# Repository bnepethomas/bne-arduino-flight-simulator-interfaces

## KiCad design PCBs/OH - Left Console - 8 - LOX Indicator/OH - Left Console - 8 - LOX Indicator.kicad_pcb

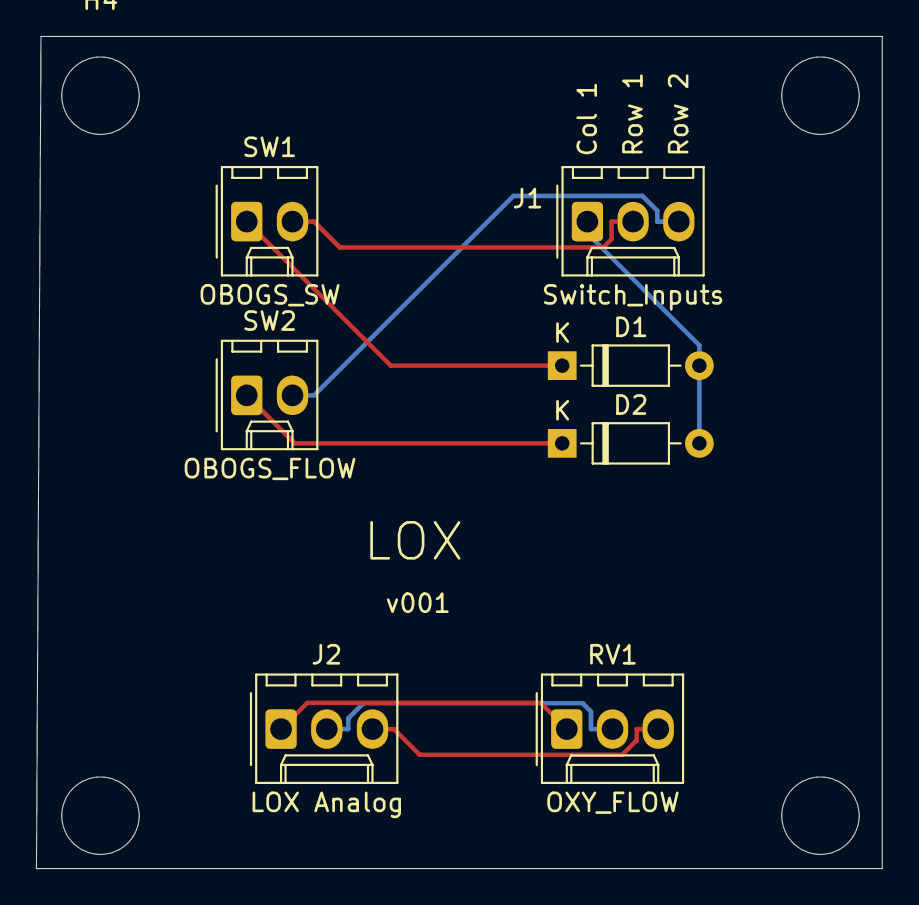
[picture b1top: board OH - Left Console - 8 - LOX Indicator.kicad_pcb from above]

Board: 2 copper layers, 47.0 x 46.2 mm, 11 parts (0 on the bottom side), 8 nets.

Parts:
D1, D2: D; D_Signal_P7.62mm_Horizontal
H1, H2, H3, H4: MountingHole; MountingHole_4.3mm_M4
J1: Switch_Inputs; Molex_1x03_P2.54mm_Vertical
J2: LOX Analog; Molex_1x03_P2.54mm_Vertical
RV1: OXY_FLOW; Molex_1x03_P2.54mm_Vertical
SW1: OBOGS_SW; Molex_1x02_P2.54mm_Vertical
SW2: OBOGS_FLOW; Molex_1x02_P2.54mm_Vertical

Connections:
/+5V: J2.1, RV1.1
/Col1: D1.2, D2.2, J1.1
/GND: J2.3, RV1.3
/Row1: J1.2, SW1.2
/Row2: J1.3, SW2.2
unnamed: D1.1, SW1.1
unnamed: D2.1, SW2.1
unnamed: J2.2, RV1.2

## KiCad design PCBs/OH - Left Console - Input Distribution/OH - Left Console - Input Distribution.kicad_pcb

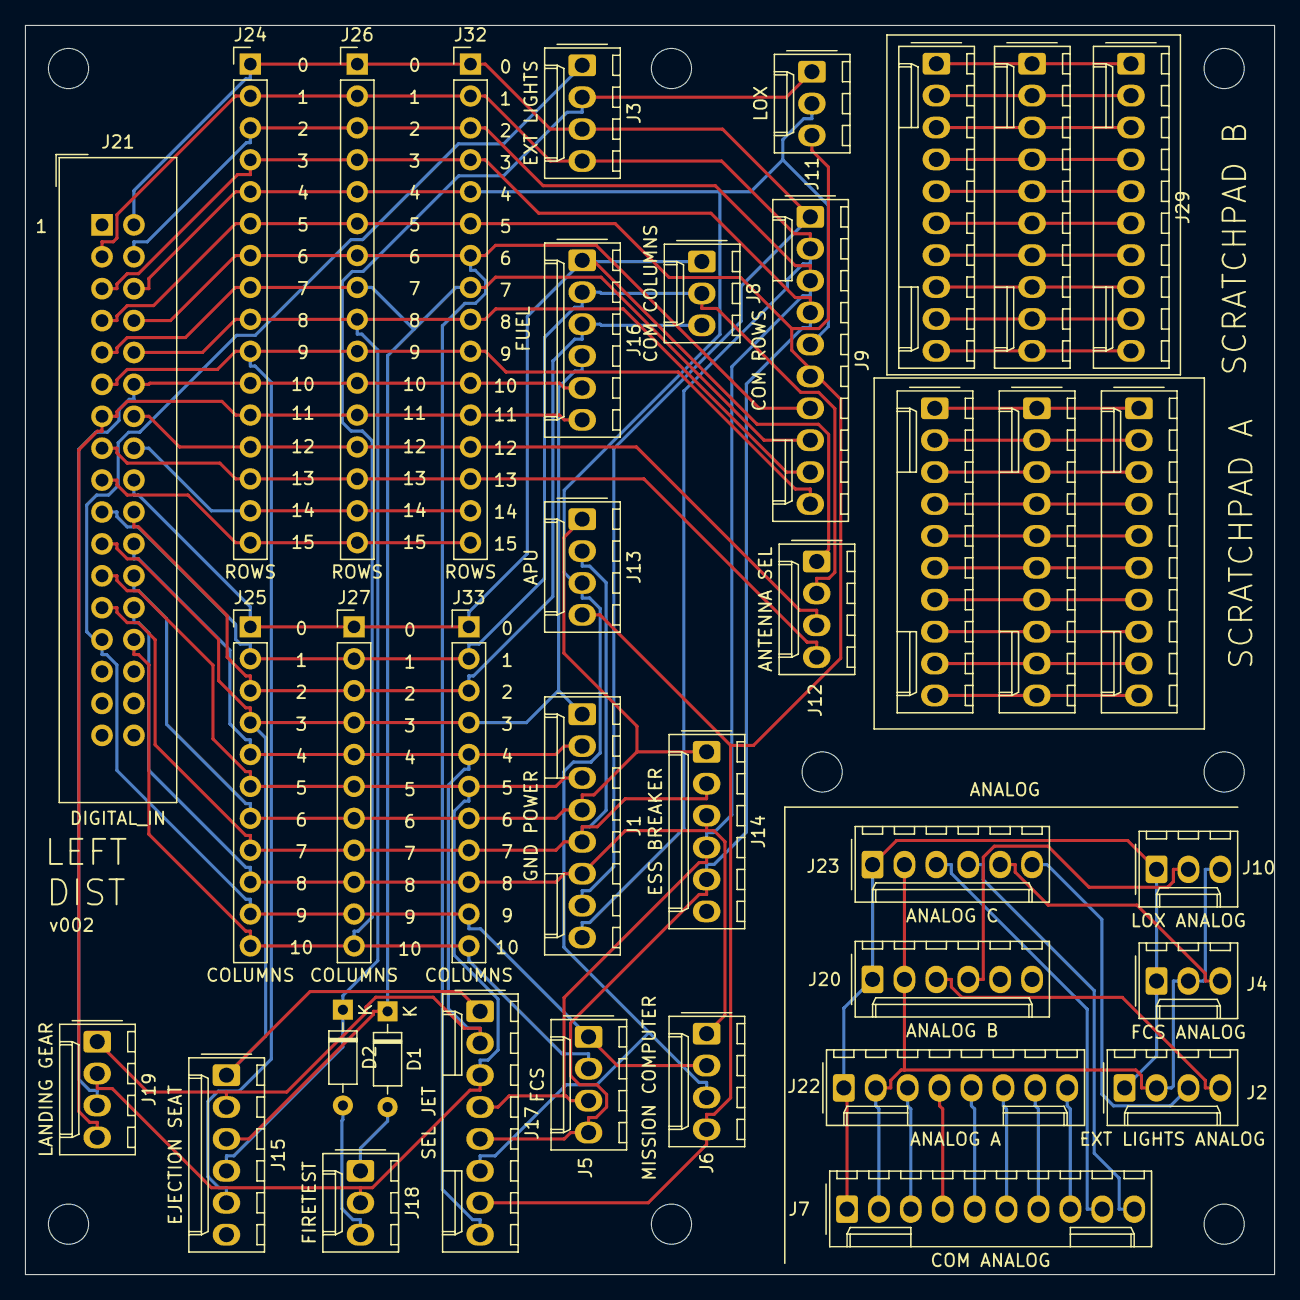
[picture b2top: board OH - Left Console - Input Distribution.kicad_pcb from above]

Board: 2 copper layers, 99.4 x 99.4 mm, 45 parts (0 on the bottom side), 63 nets.

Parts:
D1, D2: D; D_Signal_P7.62mm_Horizontal
H1, H2, H3, H4, H5, H6, H7, H8: MountingHole; MountingHole_3.2mm_M3
J1: GND POWER; Molex_1x08_P2.54mm_Vertical
J2: EXT LIGHTS ANALOG; Molex_1x04_P2.54mm_Vertical
J3: EXT LIGHTS; Molex_1x04_P2.54mm_Vertical
J4: FCS ANALOG; Molex_1x03_P2.54mm_Vertical
J5: FCS; Molex_1x04_P2.54mm_Vertical
J6: MISSION COMPUTER; Molex_1x04_P2.54mm_Vertical
J7: COM ANALOG; Molex_1x10_P2.54mm_Vertical
J8: COM COLUMNS; Molex_1x03_P2.54mm_Vertical
J9: COM ROWS; Molex_1x10_P2.54mm_Vertical
J10: LOX ANALOG; Molex_1x03_P2.54mm_Vertical
J11: LOX; Molex_1x03_P2.54mm_Vertical
J12: ANTENNA SEL; Molex_1x04_P2.54mm_Vertical
J13: APU; Molex_1x04_P2.54mm_Vertical
J14: ESS BREAKER; Molex_1x06_P2.54mm_Vertical
J15: EJECTION SEAT; Molex_1x06_P2.54mm_Vertical
J16: FUEL; Molex_1x06_P2.54mm_Vertical
J17: SEL JET; Molex_1x08_P2.54mm_Vertical
J18: FIRETEST; Molex_1x03_P2.54mm_Vertical
J19: LANDING GEAR; Molex_1x04_P2.54mm_Vertical
J20: ANALOG B; Molex_1x06_P2.54mm_Vertical
J21: DIGITAL_IN; IDC-Header_2x17_P2.54mm_Vertical
J22: ANALOG A; Molex_1x08_P2.54mm_Vertical
J23: ANALOG C; Molex_1x06_P2.54mm_Vertical
J24, J26, J32: ROWS; PinHeader_1x16_P2.54mm_Vertical
J25, J27, J33: COLUMNS; PinHeader_1x11_P2.54mm_Vertical
J28: SpareA1; Molex_1x10_P2.54mm_Vertical
J29: SpareB1; Molex_1x10_P2.54mm_Vertical
J30: SpareA2; Molex_1x10_P2.54mm_Vertical
J31: SpareB2; Molex_1x10_P2.54mm_Vertical
J34: SpareA3; Molex_1x10_P2.54mm_Vertical
J35: SpareB3; Molex_1x10_P2.54mm_Vertical

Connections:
/A1: J28.1, J30.1, J34.1
/A2: J28.2, J30.2, J34.2
/A3: J28.3, J30.3, J34.3
/A4: J28.4, J30.4, J34.4
/A5: J28.5, J30.5, J34.5
/A6: J28.6, J30.6, J34.6
/A7: J28.7, J30.7, J34.7
/A8: J28.8, J30.8, J34.8
/A9: J28.9, J30.9, J34.9
/A10: J28.10, J30.10, J34.10
/ANALOG_5V: J2.1, J4.1, J7.1, J10.1, J20.1, J22.1, J23.1
/ANALOG_GND: J2.2, J4.2, J7.2, J10.3, J20.2, J22.2, J23.2
/B1: J29.1, J31.1, J35.1
/B2: J29.2, J31.2, J35.2
/B3: J29.3, J31.3, J35.3
/B4: J29.4, J31.4, J35.4
/B5: J29.5, J31.5, J35.5
/B6: J29.6, J31.6, J35.6
/B7: J29.7, J31.7, J35.7
/B8: J29.8, J31.8, J35.8
/B9: J29.9, J31.9, J35.9
/B10: J29.10, J31.10, J35.10
/COL0: J8.1, J12.1, J16.1, J21.18, J25.1, J27.1, J33.1
/COL1: J8.2, J12.2, J16.2, J21.19, J25.2, J27.2, J33.2
/COL2: J8.3, J16.3, J21.20, J25.3, J27.3, J33.3
/COL3: J1.1, J15.1, J16.4, J17.1, J21.21, J25.4, J27.4, J33.4
/COL4: J1.2, J15.2, J17.2, J19.1, J21.22, J25.5, J27.5, J33.5
/COL5: J1.3, J17.3, J18.2, J19.2, J21.23, J25.6, J27.6, J33.6
/COL6: J1.4, J13.1, J14.1, J21.24, J25.7, J27.7, J33.7
/COL7: J1.5, J13.2, J14.2, J21.25, J25.8, J27.8, J33.8
/COL8: J1.6, J6.1, J14.3, J21.26, J25.9, J27.9, J33.9
/COL9: J3.1, J5.1, J6.2, J21.27, J25.10, J27.10, J33.10
/COL10: J3.2, J5.2, J11.1, J21.28, J25.11, J27.11, J33.11
/COM_AUX: J7.9, J23.3
/COM_ICS: J7.4, J22.4
/COM_MIDS_A: J7.6, J22.6
/COM_MIDS_B: J7.7, J22.7
/COM_RWR: J7.5, J22.5
/COM_TACAN: J7.8, J22.8
/COM_VOX: J7.3, J22.3
/COM_WPN: J7.10, J23.4
/FORMATION_DIMMER: J2.4, J20.3
/OXY_FLOW: J10.2, J20.4
/POSITION_DIMMER: J2.3, J23.6
/ROW0: J1.7, J3.3, J9.1, J21.2, J24.1, J26.1, J32.1
/ROW1: J1.8, J3.4, J9.2, J21.3, J24.2, J26.2, J32.2
/ROW2: J5.3, J9.3, J14.4, J17.4, J21.4, J24.3, J26.3, J32.3
/ROW3: J5.4, J9.4, J14.5, J17.5, J21.5, J24.4, J26.4, J32.4
/ROW4: J6.3, J9.5, J11.2, J13.3, J17.6, J21.6, J24.5, J26.5, J32.5
/ROW5: J6.4, J9.6, J11.3, J13.4, J17.7, J21.7, J24.6, J26.6, J32.6
/ROW6: J9.7, J17.8, J21.8, J24.7, J26.7, J32.7
/ROW7: D1.1, J9.8, J15.3, J21.9, J24.8, J26.8, J32.8
/ROW8: D2.1, J9.9, J15.4, J21.10, J24.9, J26.9, J32.9
/ROW9: J9.10, J15.5, J21.11, J24.10, J26.10, J32.10
/ROW10: J16.5, J19.3, J21.12, J24.11, J26.11, J32.11
/ROW11: J16.6, J19.4, J21.13, J24.12, J26.12, J32.12
/ROW12: J12.3, J21.14, J24.13, J26.13, J32.13
/ROW13: J12.4, J21.15, J24.14, J26.14, J32.14
/ROW14: J21.16, J24.15, J26.15, J32.15
/ROW15: J21.17, J24.16, J26.16, J32.16
/RUD_TRIM: J4.3, J23.5
unnamed: D1.2, J18.1
unnamed: D2.2, J18.3

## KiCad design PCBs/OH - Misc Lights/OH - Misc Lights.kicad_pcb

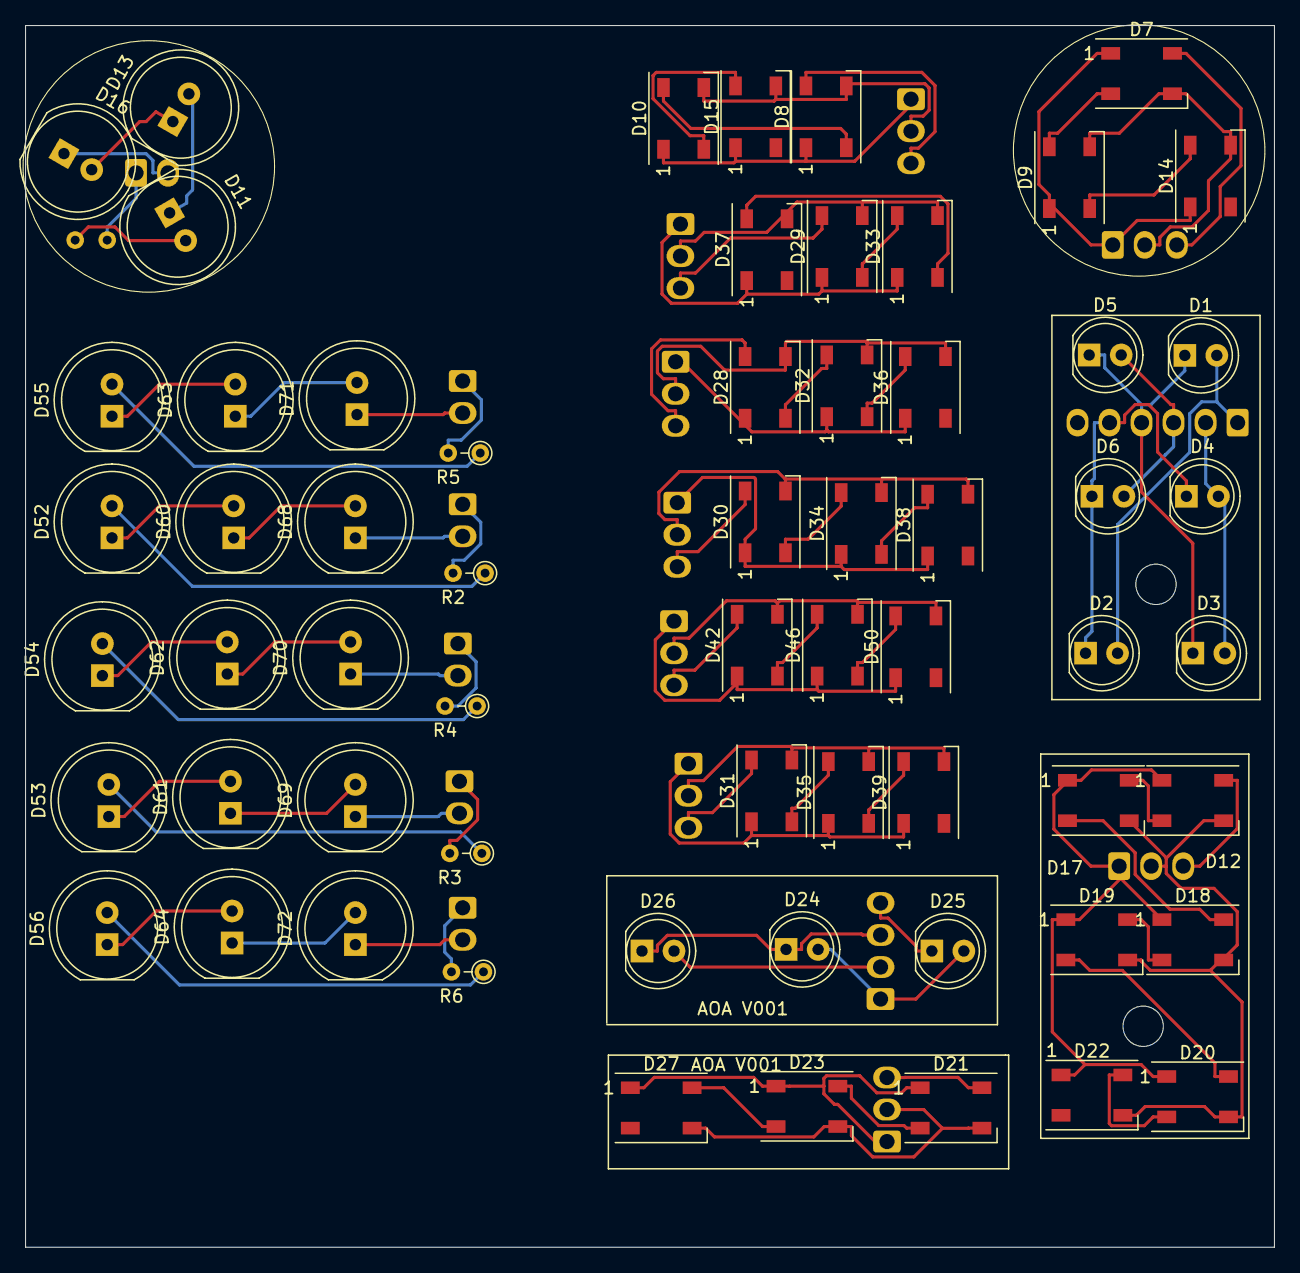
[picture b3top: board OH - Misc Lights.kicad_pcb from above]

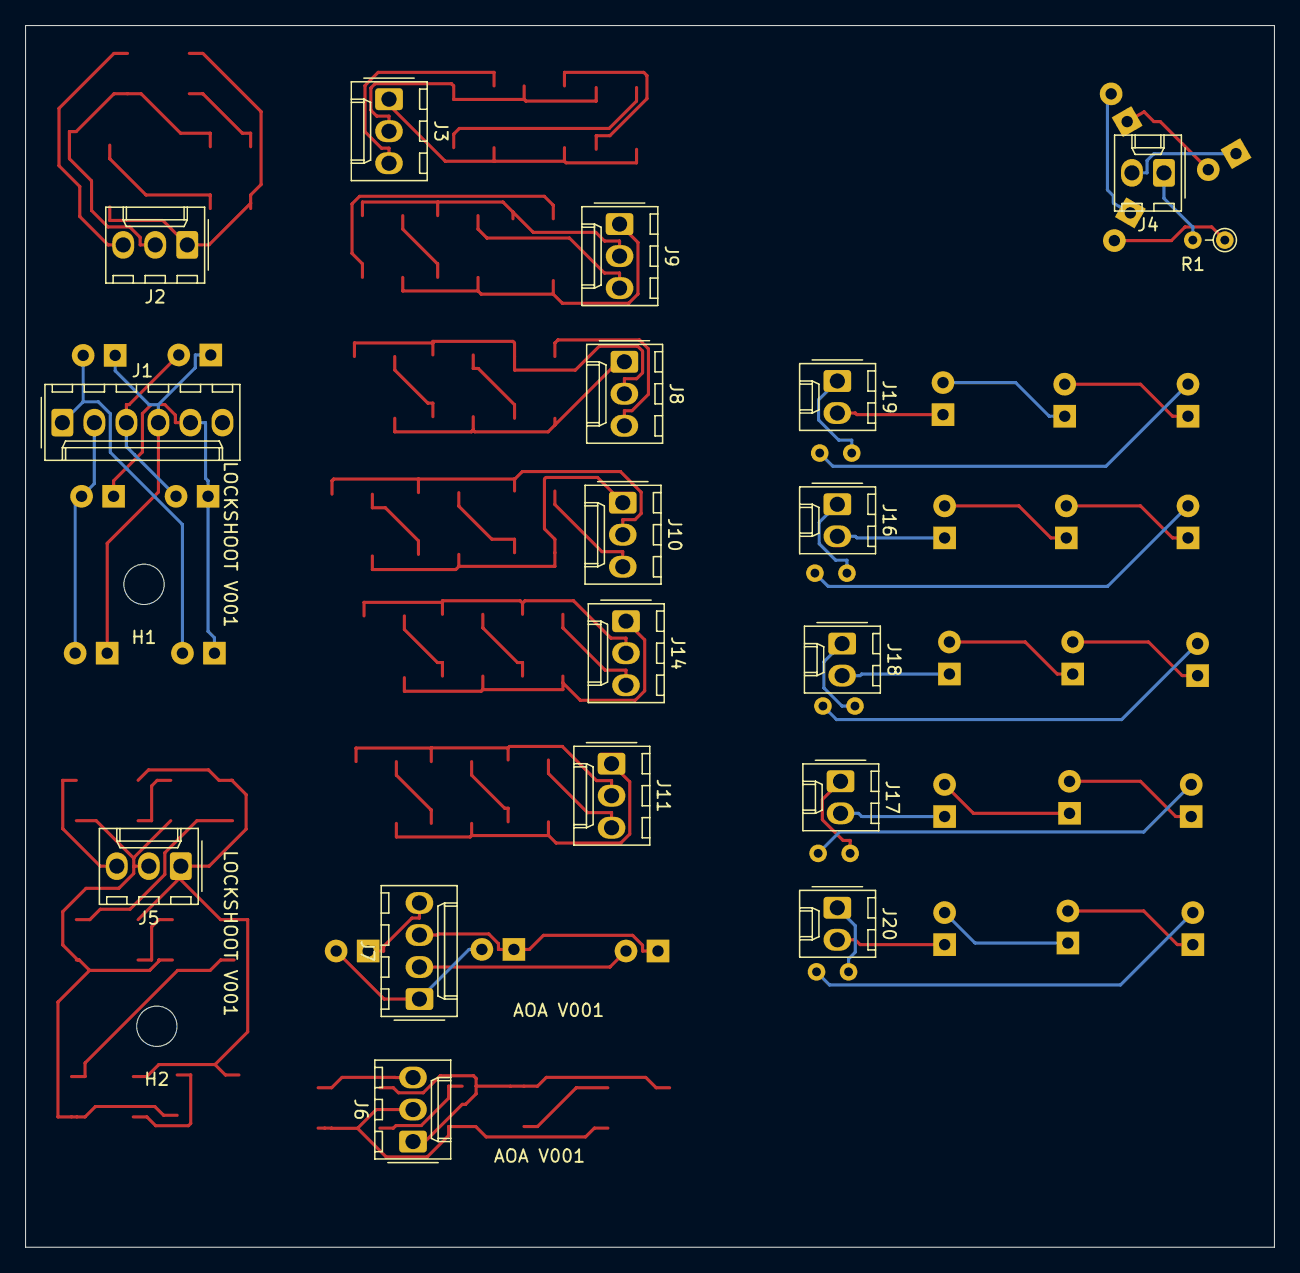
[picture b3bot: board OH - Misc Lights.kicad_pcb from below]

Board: 2 copper layers, 99.1 x 96.9 mm, 82 parts (20 on the bottom side), 87 nets.

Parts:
D1, D2, D3, D4, D5, D6, D24, D25, D26: LED; LED_D5.0mm
D7, D8, D9, D10, D12, D14, D15, D17, D18, D19, D20, D21, D22, D23, D27, D28, D29, D30, D31, D32, D33, D34, D35, D36, D37, D38, D39, D42, D46, D50: WS2812B; LED_WS2812B_PLCC4_5.0x5.0mm_P3.2mm
D11, D13, D16, D52, D53, D54, D55, D56, D60, D61, D62, D63, D64, D68, D69, D70, D71, D72: LED; LED_D8.0mm
H1, H2: MountingHole; MountingHole_3.2mm_M3
J1: Conn_01x06_Female; Molex_1x06_P2.54mm_Vertical
J2, J3, J5, J6, J8, J9, J10, J11, J14: Conn_01x03_Female; Molex_1x03_P2.54mm_Vertical
J4, J16, J17, J18, J19, J20: Conn_01x02_Female; Molex_1x02_P2.54mm_Vertical
J7: Conn_01x04_Female; Molex_1x04_P2.54mm_Vertical
R1, R2, R3, R4, R5, R6: R_US; PT_R_Axial_DIN0204_L3.6mm_D1.6mm_P2.54mm_Vertical

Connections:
/AOA_2812_+5V: D21.1, D23.1, D27.1, J6.1
/AOA_2812_GND: D21.3, D23.3, D27.3, J6.2
/AOA_2812_IN: D21.4, J6.3
/AOA_COL1: D24.2, D25.2, J7.1
/AOA_COL2: D26.2, J7.2
/AOA_ROW1: D24.1, D26.1, J7.3
/AOA_ROW2: D25.1, J7.4
/CHART_5V: J4.1, R1.2
/CHART_GND: D16.1, J4.2
/Col1: D1.2, D2.2, J1.1
/Col2: D3.2, D4.2, J1.2
/Col3: D5.2, D6.2, J1.3
/FLOOD_2812_+5V: D7.1, D9.1, D14.1, J2.1
/FLOOD_2812_GND: D7.3, D9.3, D14.3, J2.2
/FLOOD_2812_IN: D7.4, J2.3
/LOCKSHOOT_2812_+5V: D12.1, D17.1, D18.1, D19.1, D20.1, D22.1, J5.1
/LOCKSHOOT_2812_GND: D12.3, D17.3, D18.3, D19.3, D20.3, D22.3, J5.2
/LOCKSHOOT_IN: D12.4, J5.3
/Row1: D1.1, D3.1, D5.1, J1.4
/Row2: D2.1, D4.1, D6.1, J1.5
unnamed: D7.2, D9.4
unnamed: D8.4, J3.3
unnamed: D8.1, D10.1, D15.1, J3.1
unnamed: D10.2, D15.4
unnamed: D8.3, D10.3, D15.3, J3.2
unnamed: D8.2, D10.4
unnamed: D11.1, D13.2
unnamed: D11.2, R1.1
unnamed: D12.2, D17.4
unnamed: D13.1, D16.2
unnamed: D9.2, D14.4
unnamed: D17.2, D18.4
unnamed: D18.2, D19.4
unnamed: D19.2, D20.4
unnamed: D20.2, D22.4
unnamed: D21.2, D23.4
unnamed: D23.2, D27.4
unnamed: D28.1, D32.1, D36.1, J8.1
unnamed: D28.2, D32.4
unnamed: D28.3, D32.3, D36.3, J8.2
unnamed: D28.4, J8.3
unnamed: D29.1, D33.1, D37.1, J9.1
unnamed: D29.2, D33.4
unnamed: D29.3, D33.3, D37.3, J9.2
unnamed: D29.4, J9.3
unnamed: D30.1, D34.1, D38.1, J10.1
unnamed: D30.2, D34.4
unnamed: D30.3, D34.3, D38.3, J10.2
unnamed: D30.4, J10.3
unnamed: D31.1, D35.1, D39.1, J11.1
unnamed: D31.2, D35.4
unnamed: D31.3, D35.3, D39.3, J11.2
unnamed: D31.4, J11.3
unnamed: D32.2, D36.4
unnamed: D33.2, D37.4
unnamed: D34.2, D38.4
unnamed: D35.2, D39.4
unnamed: D42.1, D46.1, D50.1, J14.1
unnamed: D42.2, D46.4
unnamed: D42.3, D46.3, D50.3, J14.2
unnamed: D42.4, J14.3
unnamed: D46.2, D50.4
unnamed: D52.1, D60.2
unnamed: D52.2, R2.1
unnamed: D53.1, D61.2
unnamed: D53.2, R3.1
unnamed: D54.1, D62.2
unnamed: D54.2, R4.1
unnamed: D55.1, D63.2
unnamed: D55.2, R5.1
unnamed: D56.1, D64.2
unnamed: D56.2, R6.1
unnamed: D60.1, D68.2
unnamed: D61.1, D69.2
unnamed: D62.1, D70.2
unnamed: D63.1, D71.2
unnamed: D64.1, D72.2
unnamed: D68.1, J16.2
unnamed: D69.1, J17.2
unnamed: D70.1, J18.2
unnamed: D71.1, J19.2
unnamed: D72.1, J20.2
unnamed: J16.1, R2.2
unnamed: J17.1, R3.2
unnamed: J18.1, R4.2
unnamed: J19.1, R5.2
unnamed: J20.1, R6.2

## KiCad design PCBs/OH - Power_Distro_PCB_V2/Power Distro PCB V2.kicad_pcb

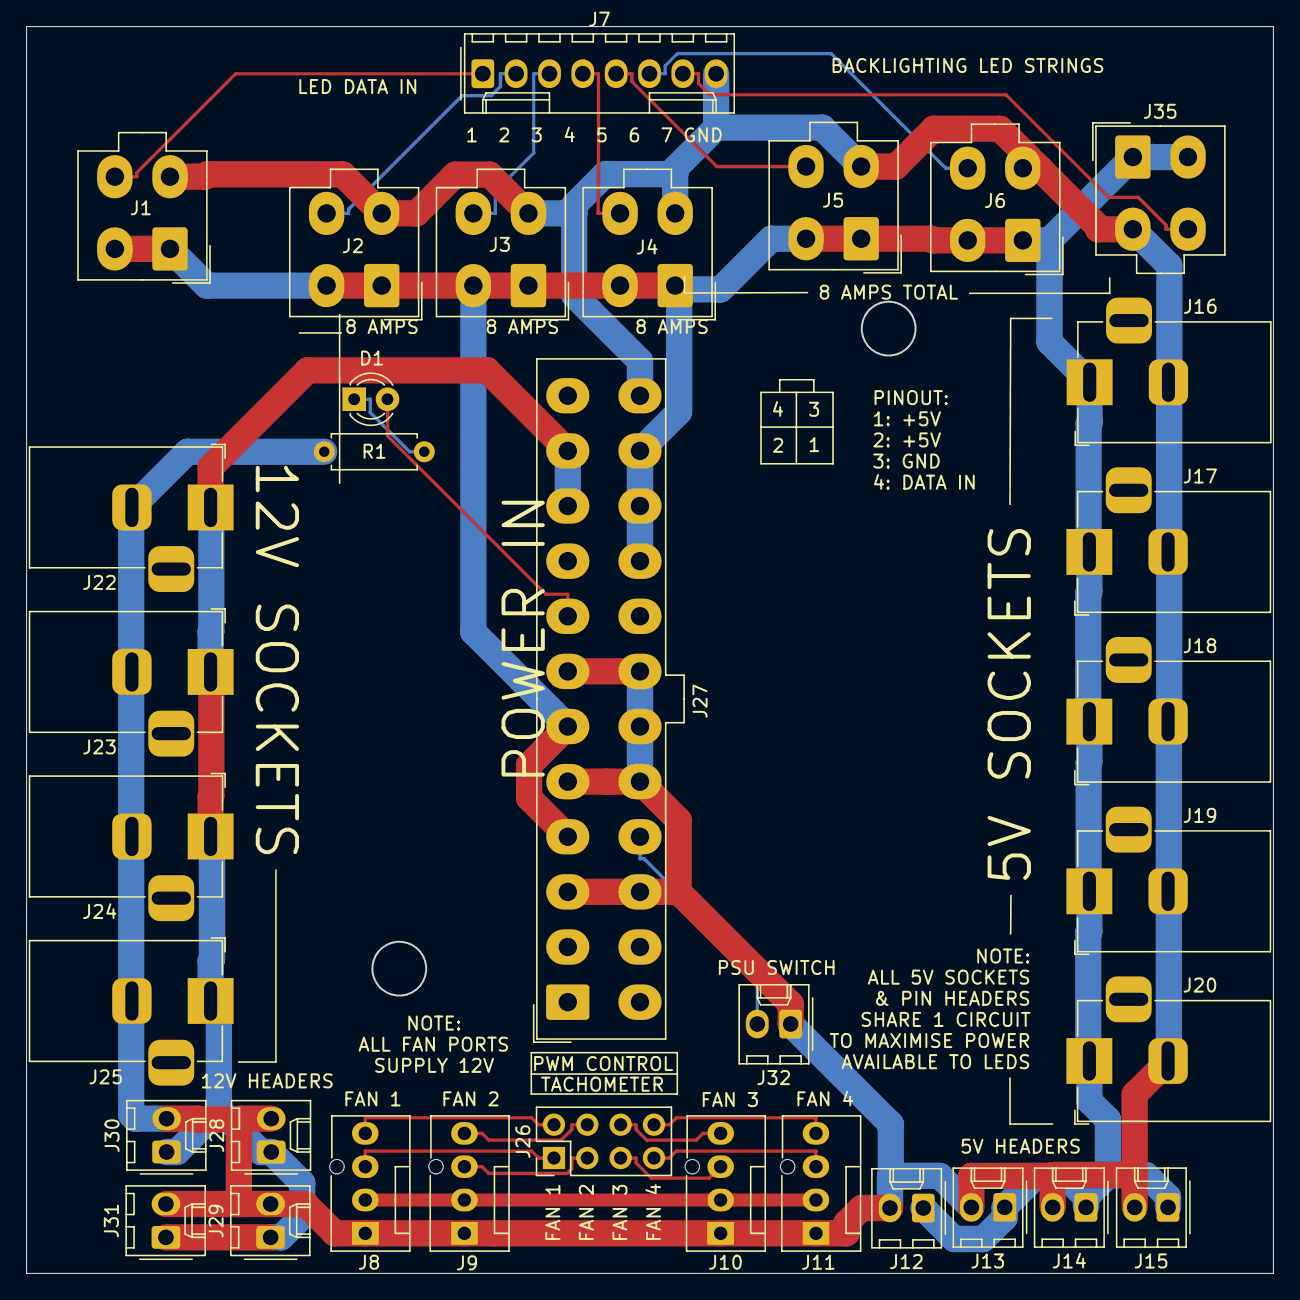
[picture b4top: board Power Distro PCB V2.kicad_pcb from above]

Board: 2 copper layers, 95.0 x 95.0 mm, 34 parts (0 on the bottom side), 22 nets.

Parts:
D1: LED; LED_D3.0mm
J1, J2, J3, J4, J5, J6, J35: Conn_01x04_Female; Molex_Mini-Fit_Jr_5566-04A_2x02_P4.20mm_Vertical
J7: Conn_01x08_Female; Molex_1x08_P2.54mm_Vertical
J8, J9, J10, J11: Conn_01x04_Female; FanPinHeader_1x04_P2.54mm_Vertical
J12, J13, J14, J15, J28, J29, J30, J31, J32: Conn_01x02_Female; Molex_KK-254_AE-6410-02A_1x02_P2.54mm_Vertical
J16, J17, J18, J19, J20, J22, J23, J24, J25: Conn_01x02_Female; BarrelJack_Horizontal
J26: Conn_01x08_Female; PinHeader_2x04_P2.54mm_Vertical
J27: Conn_01x24_Female; Molex_Mini-Fit_Jr_5566-24A_2x12_P4.20mm_Vertical
R1: R; R_Axial_DIN0207_L6.3mm_D2.5mm_P7.62mm_Horizontal

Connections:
/12VSOCKETS+: J22.1, J23.1, J24.1, J25.1, J27.10, J27.11, J28.1, J29.1, J30.1, J31.1
/FAN1Control: J8.4, J26.2
/FAN1Tach: J8.3, J26.1
/FAN2Control: J9.4, J26.4
/FAN2Tach: J9.3, J26.3
/FAN3Control: J10.4, J26.6
/FAN3Tach: J10.3, J26.5
/FAN4Control: J11.4, J26.8
/FAN4Tach: J11.3, J26.7
/FAN+: J8.2, J9.2, J10.2, J11.2
/LED5V1: J1.1, J1.2, J2.1, J2.2, J3.1, J3.2, J4.1, J4.2, J5.1, J5.2, J6.1, J6.2, J12.1, J13.1, J14.1, J15.1, J16.1, J17.1, J18.1, J19.1, J20.1, J27.4, J27.6, J27.21, J27.22, J27.23, J35.1, J35.2
/LEDDATA1: J1.4, J7.1
/LEDDATA2: J2.4, J7.2
/LEDDATA3: J3.4, J7.3
/LEDDATA4: J4.4, J7.4
/LEDDATA5: J5.4, J7.5
/LEDDATA6: J6.4, J7.6
/LEDDATA7: J7.7, J35.4
/LEDGND: J1.3, J2.3, J3.3, J4.3, J5.3, J6.3, J7.8, J8.1, J9.1, J10.1, J11.1, J12.2, J13.2, J14.2, J15.2, J16.2, J17.2, J18.2, J19.2, J20.2, J22.2, J23.2, J24.2, J25.2, J27.3, J27.5, J27.7, J27.15, J27.17, J27.18, J27.19, J27.24, J28.2, J29.2, J30.2, J31.2, J32.1, J35.3, R1.1
/PSUSW: J27.16, J32.2
/PWRGOOD: D1.2, J27.8
unnamed: D1.1, R1.2

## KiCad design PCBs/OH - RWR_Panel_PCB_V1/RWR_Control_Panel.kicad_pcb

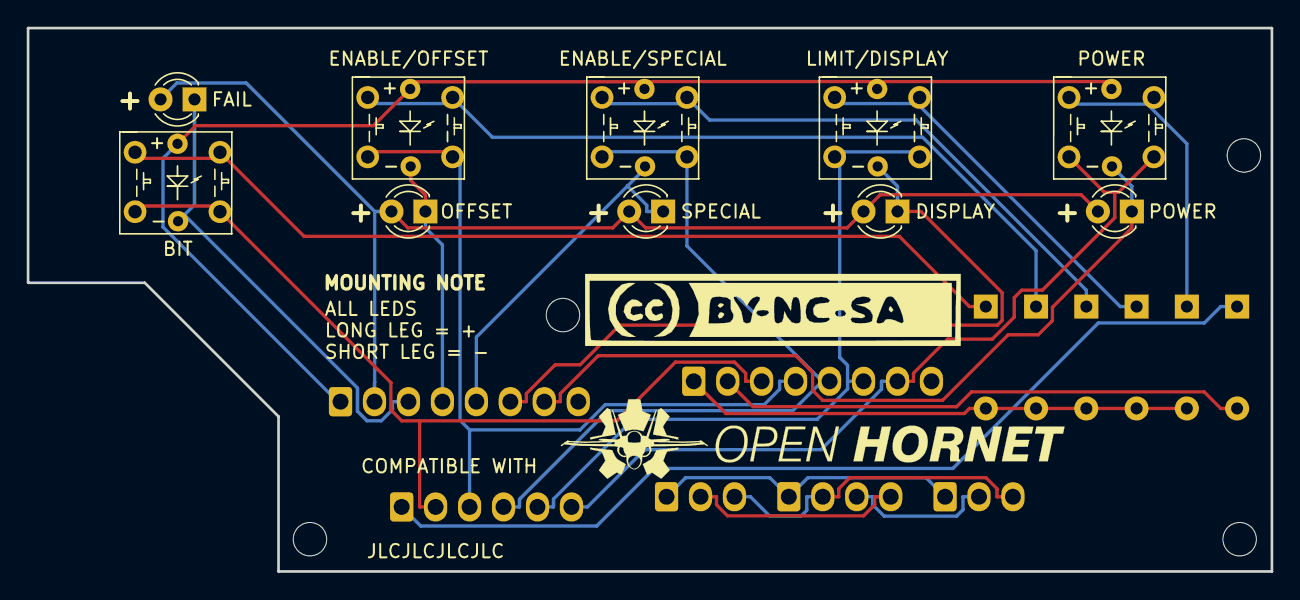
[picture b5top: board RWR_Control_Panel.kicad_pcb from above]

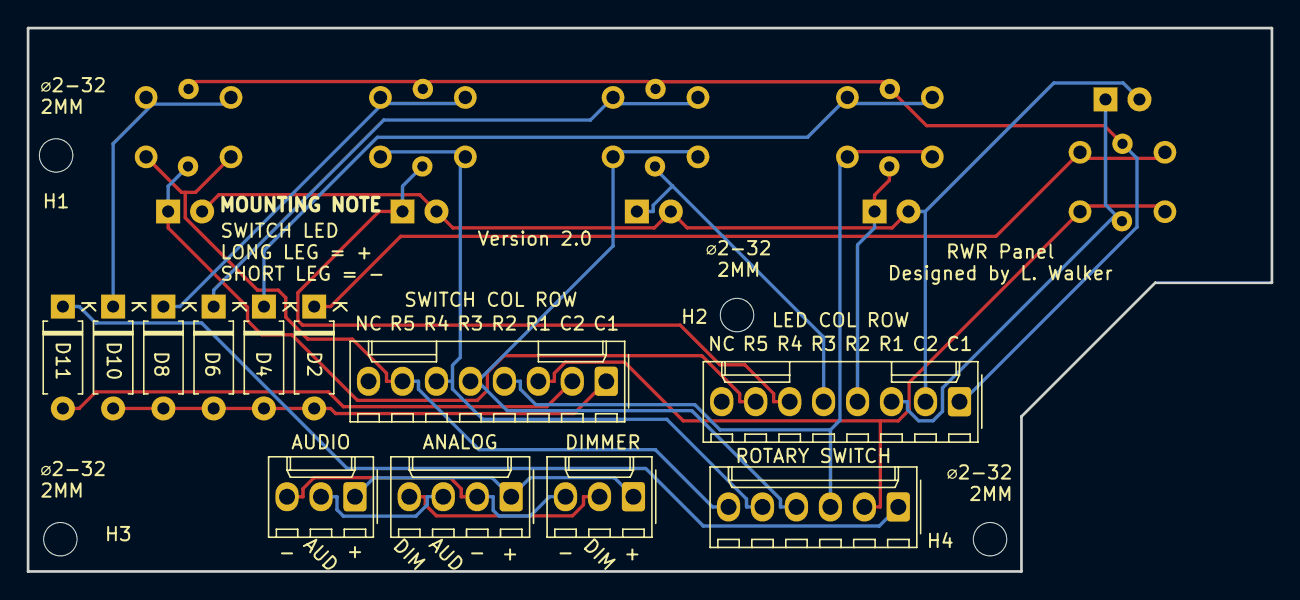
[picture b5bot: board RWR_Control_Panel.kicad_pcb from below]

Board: 2 copper layers, 93.0 x 40.6 mm, 26 parts (12 on the bottom side), 24 nets.

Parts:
BIT: PT_Tactile_Switch_Led; PT_Small_Tactile_Switch_With_LED
D1: FAIL; LED_D3.0mm
D2, D4, D6, D8, D10, D11: D; D_A-405_P7.62mm_Horizontal
D3: OFFSET; LED_D3.0mm
D5: SPECIAL; LED_D3.0mm
D7: DISPLAY; LED_D3.0mm
D9: POWER; LED_D3.0mm
ENABLE/OFFSET: PT_Tactile_Switch_Led; PT_Small_Tactile_Switch_With_LED
ENABLE/SPECIAL: PT_Tactile_Switch_Led; PT_Small_Tactile_Switch_With_LED
J1: LED COL ROW; Molex_KK-254_AE-6410-08A_1x08_P2.54mm_Vertical
J2: DIMMER; Molex_KK-254_AE-6410-03A_1x03_P2.54mm_Vertical
J3: AUDIO; Molex_KK-254_AE-6410-03A_1x03_P2.54mm_Vertical
J4: ROTARY SWITCH; Molex_KK-254_AE-6410-06A_1x06_P2.54mm_Vertical
J5: ANALOG; Molex_KK-254_AE-6410-04A_1x04_P2.54mm_Vertical
J6: SWITCH COL ROW; Molex_KK-254_AE-6410-08A_1x08_P2.54mm_Vertical
LIMIT/DISPLAY: PT_Tactile_Switch_Led; PT_Small_Tactile_Switch_With_LED
P3, P4, P5, P6: CONN_01X01; MountingHole_2.5mm
POWER: PT_Tactile_Switch_Led; PT_Small_Tactile_Switch_With_LED

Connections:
/Analog5V: J2.1, J3.1, J5.1
/AnalogAudio: J2.2, J5.3
/AnalogDimmer: J3.2, J5.4
/AnalogGND: J2.3, J3.3, J5.2
/Col1: D2.2, D4.2, D6.2, D8.2, D10.2, J6.1
/Col2: D11.2, J6.2
/Row1: BIT.3, BIT.4, J4.2, J6.3
/Row2: ENABLE/OFFSET.3, ENABLE/OFFSET.4, J4.3, J6.4
/Row3: ENABLE/SPECIAL.3, ENABLE/SPECIAL.4, J4.4, J6.5
/Row4: J4.5, J6.6, LIMIT/DISPLAY.3, LIMIT/DISPLAY.4
/Row5: J4.6, J6.7, POWER.3, POWER.4
/ledcol1: BIT.5, ENABLE/OFFSET.5, ENABLE/SPECIAL.5, J1.1, LIMIT/DISPLAY.5, POWER.5
/ledcol2: D1.2, D3.2, D5.2, D7.2, D9.2, J1.2
/ledrow1: BIT.6, D1.1, J1.3
/ledrow2: D3.1, ENABLE/OFFSET.6, J1.4
/ledrow3: D5.1, ENABLE/SPECIAL.6, J1.5
/ledrow4: D7.1, J1.6, LIMIT/DISPLAY.6
/ledrow5: D9.1, J1.7, POWER.6
unnamed: BIT.1, BIT.2, D2.1
unnamed: D4.1, ENABLE/OFFSET.1, ENABLE/OFFSET.2
unnamed: D6.1, ENABLE/SPECIAL.1, ENABLE/SPECIAL.2
unnamed: D8.1, LIMIT/DISPLAY.1, LIMIT/DISPLAY.2
unnamed: D10.1, POWER.1, POWER.2
unnamed: D11.1, J4.1

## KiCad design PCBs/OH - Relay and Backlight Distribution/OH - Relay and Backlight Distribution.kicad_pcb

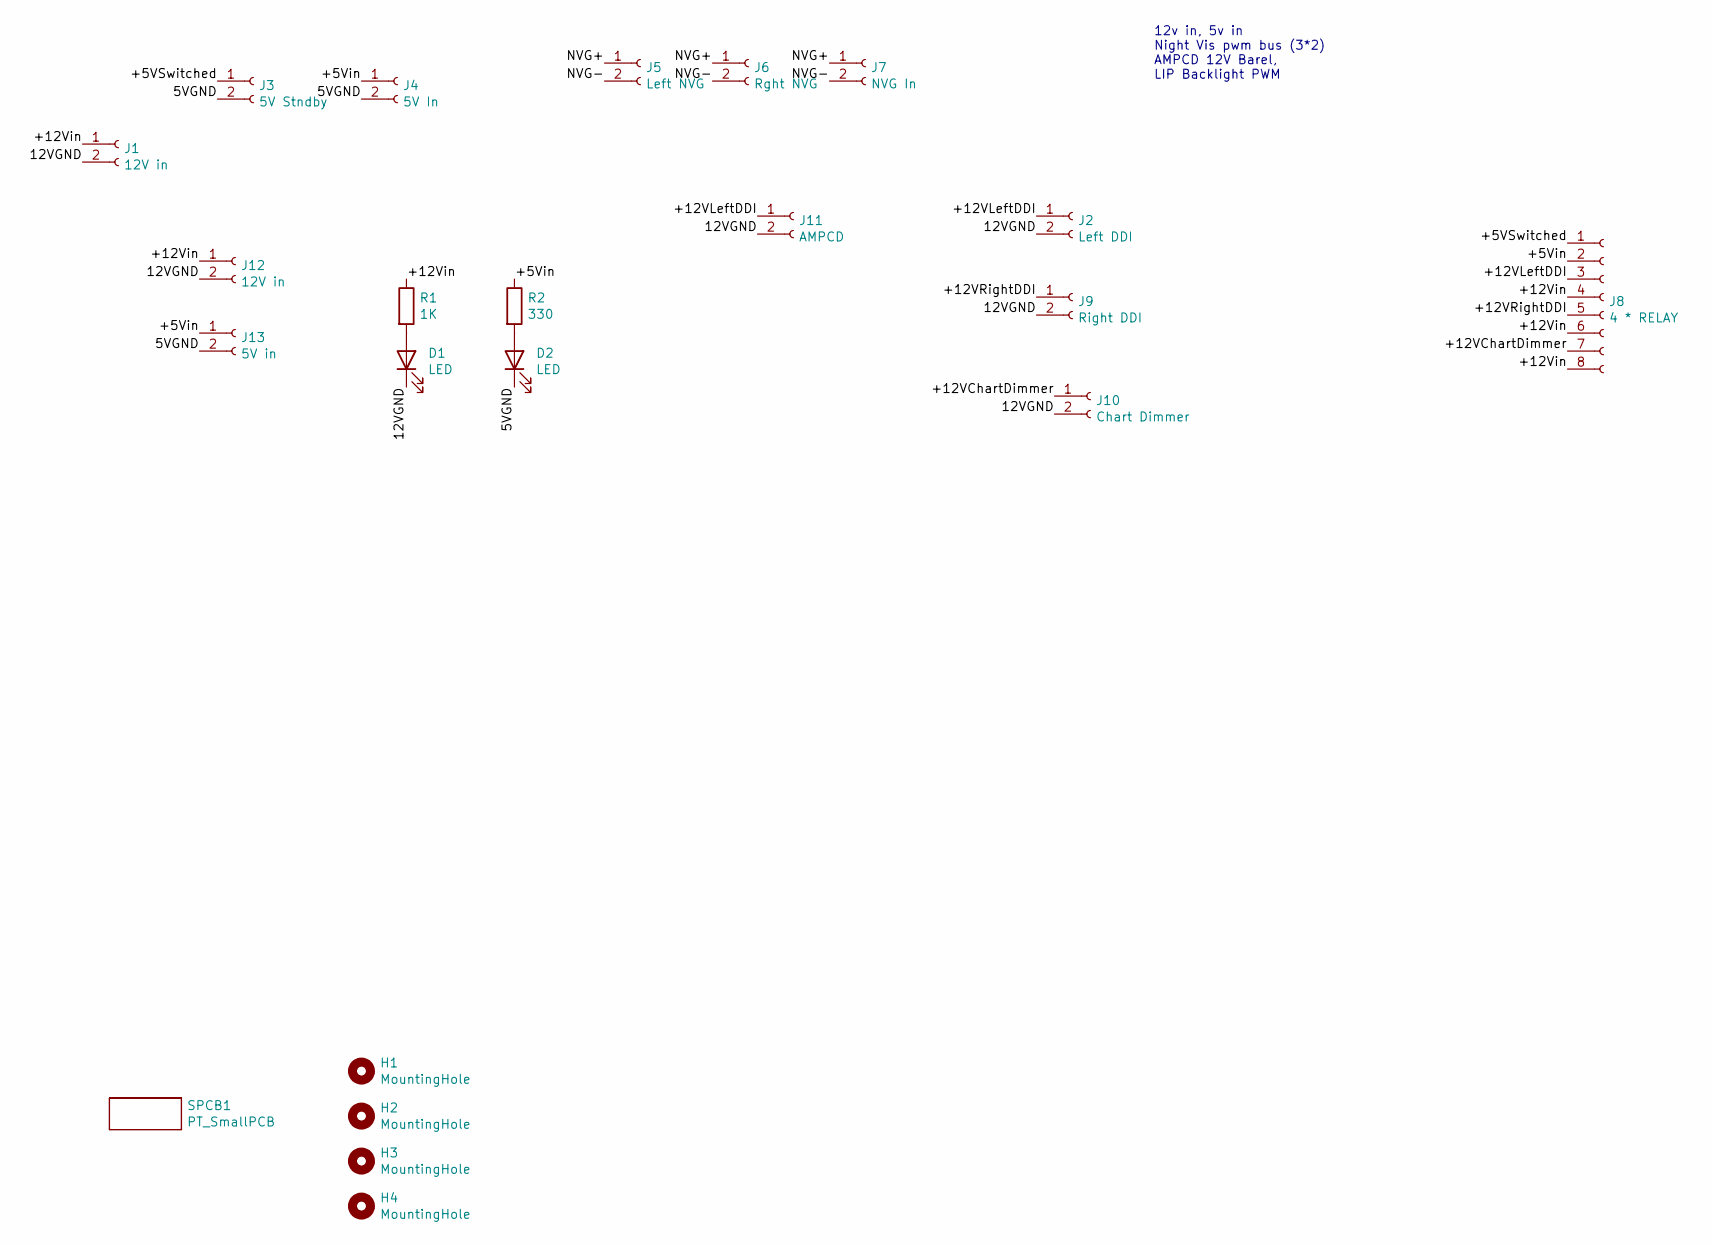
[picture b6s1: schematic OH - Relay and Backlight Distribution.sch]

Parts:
D1, D2: LED; LED_D3.0mm
H1, H2, H3, H4: MountingHole; MountingHole_3.2mm_M3
J1: 12V in; BarrelJack_Horizontal
J2: Left DDI; Molex_KK-254_AE-6410-02A_1x02_P2.54mm_Vertical
J3: 5V Stndby; BarrelJack_Horizontal
J4: 5V In; BarrelJack_Horizontal
J5: Left NVG; Molex_KK-254_AE-6410-02A_1x02_P2.54mm_Vertical
J6: Rght NVG; Molex_KK-254_AE-6410-02A_1x02_P2.54mm_Vertical
J7: NVG In; Molex_KK-254_AE-6410-02A_1x02_P2.54mm_Vertical
J8: 4 * RELAY; Molex_KK-254_AE-6410-08A_1x08_P2.54mm_Vertical
J9: Right DDI; Molex_KK-254_AE-6410-02A_1x02_P2.54mm_Vertical
J10: Chart Dimmer; Molex_KK-254_AE-6410-02A_1x02_P2.54mm_Vertical
J11: AMPCD; BarrelJack_Horizontal
J12: 12V in; Molex_KK-254_AE-6410-02A_1x02_P2.54mm_Vertical
J13: 5V in; Molex_KK-254_AE-6410-02A_1x02_P2.54mm_Vertical
R1: 1K; R_Axial_DIN0207_L6.3mm_D2.5mm_P7.62mm_Horizontal
R2: 330; R_Axial_DIN0207_L6.3mm_D2.5mm_P7.62mm_Horizontal
SPCB1: PT_SmallPCB; PT_General_PCB_Outline

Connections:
/5VGND: D2.1 (K), J3.2, J4.2, J13.2
/12VGND: D1.1 (K), J1.2, J2.2, J9.2, J10.2, J11.2, J12.2
/+5VSwitched: J3.1, J8.1
/+5Vin: J4.1, J8.2, J13.1, R2.1
/+12VChartDimmer: J8.7, J10.1
/+12VLeftDDI: J2.1, J8.3, J11.1
/+12VRightDDI: J8.5, J9.1
/+12Vin: J1.1, J8.4, J8.6, J8.8, J12.1, R1.1
/NVG+: J5.1, J6.1, J7.1
/NVG-: J5.2, J6.2, J7.2
unnamed: D1.2 (A), R1.2
unnamed: D2.2 (A), R2.2

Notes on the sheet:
12v in, 5v in Night Vis pwm bus (3*2) AMPCD 12V Barel, LIP Backlight PWM

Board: 2 copper layers, 22 parts (0 on the bottom side), 12 nets, no tracks yet.

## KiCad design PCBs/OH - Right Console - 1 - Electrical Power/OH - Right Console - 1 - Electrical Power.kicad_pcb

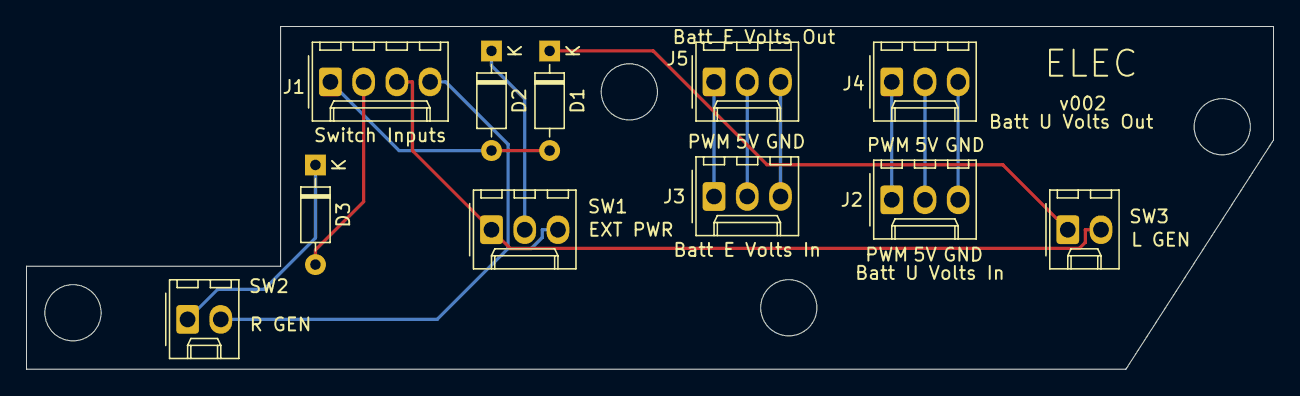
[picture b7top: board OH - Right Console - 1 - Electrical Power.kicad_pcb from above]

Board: 2 copper layers, 95.4 x 26.2 mm, 15 parts (0 on the bottom side), 13 nets.

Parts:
D1, D2, D3: D; D_Signal_P7.62mm_Horizontal
H1, H2, H3, H4: MountingHole; MountingHole_4.3mm_M4
J1: Switch Inputs; Molex_1x04_P2.54mm_Vertical
J2: Batt U Volts In; Molex_1x03_P2.54mm_Vertical
J3: Batt E Volts In; Molex_1x03_P2.54mm_Vertical
J4: Batt U Volts Out; Molex_1x03_P2.54mm_Vertical
J5: Batt E Volts Out; Molex_1x03_P2.54mm_Vertical
SW1: EXT PWR; Molex_1x03_P2.54mm_Vertical
SW2: R GEN; Molex_1x02_P2.54mm_Vertical
SW3: L GEN; Molex_1x02_P2.54mm_Vertical

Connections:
/E_5V: J3.2, J5.2
/E_GND: J3.3, J5.3
/E_PWM: J3.1, J5.1
/Row1: J1.3, SW1.1, SW3.2
/Row2: J1.4, SW1.3, SW2.2
/U_5V: J2.2, J4.2
/U_GND: J2.3, J4.3
/U_PWM: J2.1, J4.1
unnamed: D1.1, SW3.1
unnamed: D1.2, D2.2, J1.1
unnamed: D2.1, SW1.2
unnamed: D3.1, SW2.1
unnamed: D3.2, J1.2

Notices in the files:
PCBs/OH - Power_Distro_PCB_V2/Power Distro PCB V2.kicad_pcb:
© L. Walker 2021
